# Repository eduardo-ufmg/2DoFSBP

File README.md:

# 2DoFSBP
A two degrees of freedom self balancing pendulum.
3D Drawing: https://cad.onshape.com/documents/dcaab3bd08b5da9e1fdd55d0/

# TODO

## Printing
- [ ] Print a half-wheel pair
- [ ] Conclude motor identification before proceeding
- [ ] Print and test a motor connector
- [ ] Print and test the base
- [ ] Print and test a connector for the wheel guard
- [ ] Print and test a wheel guard
- [ ] Print and test the second set

## Motor Identification
- [ ] Test motor
- [ ] Gather the following information
  - Is the PWM signal active low or active high?
  - Which level in the motor's DIR pin makes it rotate counterclockwise (from the motor's perspective, rather than facing its front)?
  - When the motor is rotating counterclockwise, does the encoder output from [this api](https://github.com/madhephaestus/ESP32Encoder) increment or decrement? (use attachFullQuad and consider 400 pulses per revolution)
- [ ] Create a class for the motor
  - Input signal must be a float in [-1, 1]
  - -1 → max speed clockwise, 1 → max speed counterclockwise
- [ ] Create a class for the encoder
  - Counterclockwise movement increments its position, clockwise decrements it
- [ ] Test both classes
- [ ] Write the code for the identification procedure
  - [ ] Microcontroller
    - Not supposed to compute speed online. Simply collect and transmit the encoder position readings.
    - Use a series of steps large enough for it to approach steady state, but not enough for it to reach it. (See PRBS identification)
    - Collect the input signal to the motor's object and the output signal from the encoder's object at 10 ms
    - Send data to the host at each sampling
    - Avoid blocking operations
  - [ ] Host
    - Listen for the experiment data
    - Store the experiment data when it is finished
    - Preprocess it
      - Remove invalid lines
      - Compute speed and acceleration from the position
    - Fit a standard DC motor transfer function
    - Store it and any available statistic about it
    - Extend it so U(s) is the input signal to the motor's object and Y(s) is the wheel torque
- [ ] Write the code for the model validation procedure
  - [ ] Microcontroller
    - Use the same code that was used for the identification
  - [ ] Host
    - Same acquisition and preprocessing as in the identification procedure
    - Simulate the model for the collected input
    - Compare its output to the captured output from the system

## Pendulum Modeling
- [ ] Capture a simplified geometric model
- [ ] Model the MIMO system with inputs T1 and T2 and outputs Theta and Phi, where:
  - T1 is the torque of the motor that controls Theta
  - T2 is the torque of the motor that controls Phi
  - Theta is the pitch angle
  - Phi is the roll angle
  - Coupling is to be considered

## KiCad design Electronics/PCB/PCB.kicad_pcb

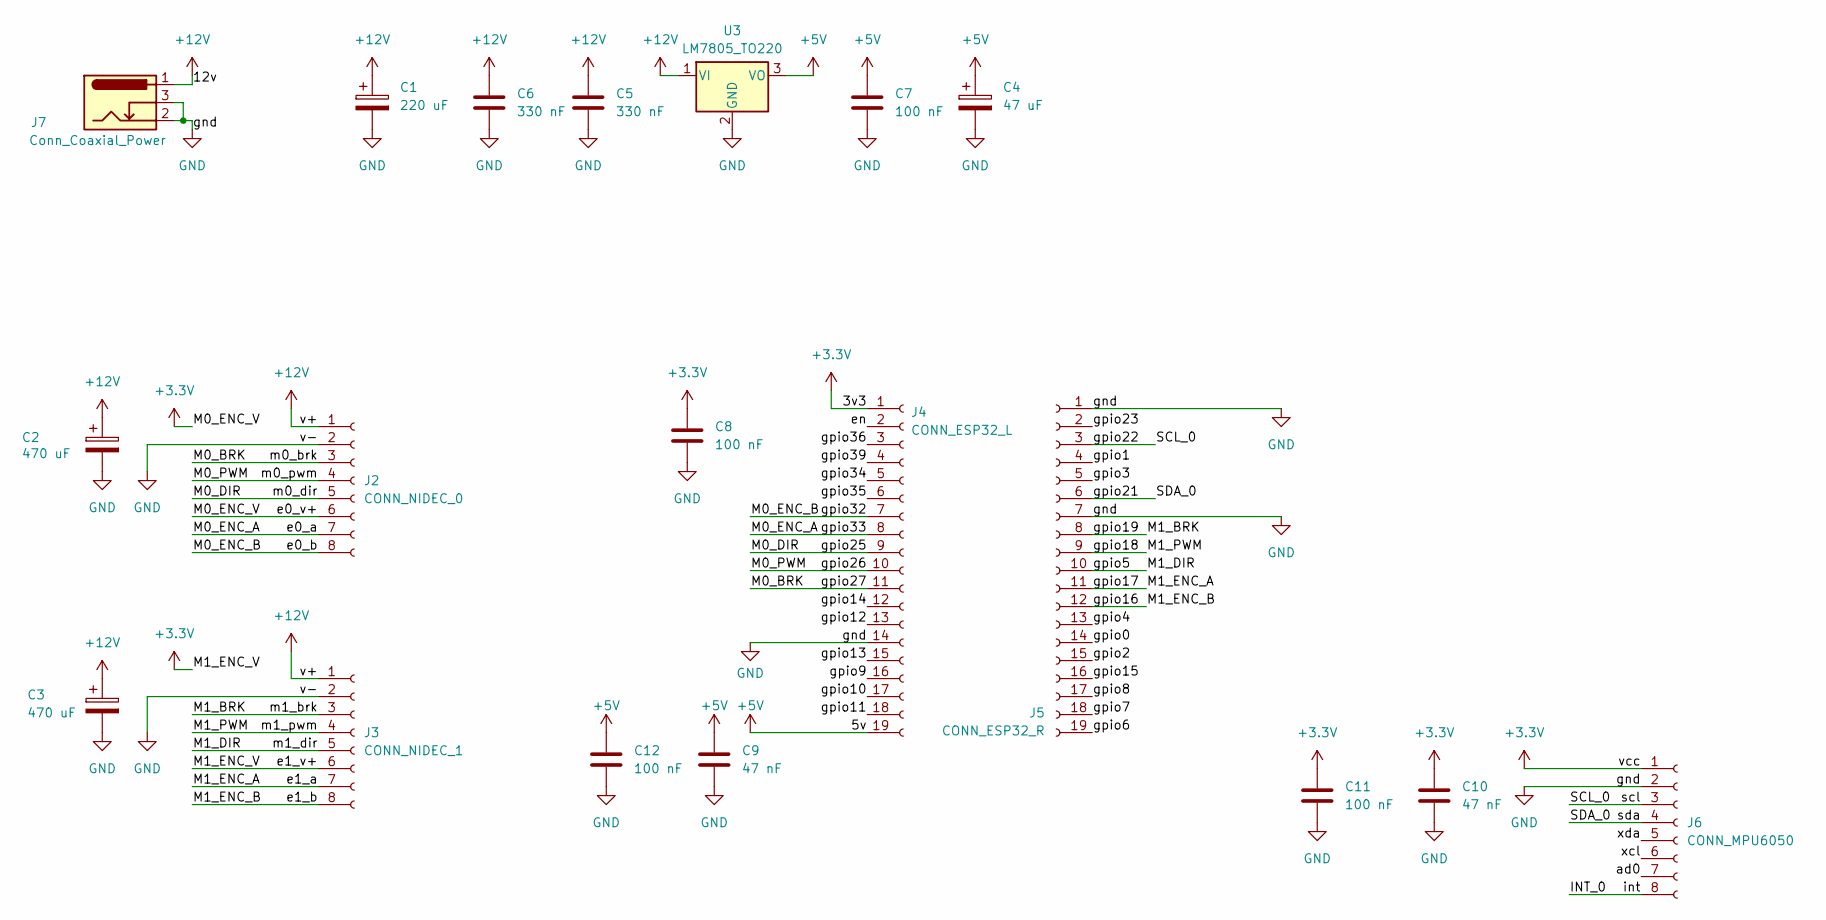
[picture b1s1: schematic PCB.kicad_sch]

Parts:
C1: 220 uF; CP_Radial_D8.0mm_P3.50mm
C2, C3: 470 uF; CP_Radial_D10.0mm_P5.00mm
C4: 47 uF; CP_Radial_D6.3mm_P2.50mm
C5, C6: 330 nF; C_Rect_L7.0mm_W2.5mm_P5.00mm
C7, C8, C11, C12: 100 nF; C_Disc_D3.0mm_W2.0mm_P2.50mm
C9, C10: 47 nF; C_Disc_D3.0mm_W2.0mm_P2.50mm
J2: CONN_NIDEC_0; JST_EH_B8B-EH-A_1x08_P2.50mm_Vertical
J3: CONN_NIDEC_1; JST_EH_B8B-EH-A_1x08_P2.50mm_Vertical
J4: CONN_ESP32_L; PinSocket_1x19_P2.54mm_Vertical
J5: CONN_ESP32_R; PinSocket_1x19_P2.54mm_Vertical
J6: CONN_MPU6050; PinSocket_1x08_P2.54mm_Vertical
J7: Conn_Coaxial_Power; BarrelJack_Horizontal
U3: LM7805_TO220; TO-220-3_Vertical

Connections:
+3.3V: C8.1, C10.1, C11.1, J2.6, J3.6, J4.1, J6.1
+5V: C4.1, C7.1, C9.1, C12.1, J4.19, U3.3 (VO)
+12V: C1.1, C2.1, C3.1, C5.1, C6.1, J2.1, J3.1, J7.1, U3.1 (VI)
/INT_0: J6.8
/M0_BRK: J2.3, J4.11
/M0_DIR: J2.5, J4.9
/M0_ENC_A: J2.7, J4.8
/M0_ENC_B: J2.8, J4.7
/M0_PWM: J2.4, J4.10
/M1_BRK: J3.3, J5.8
/M1_DIR: J3.5, J5.10
/M1_ENC_A: J3.7, J5.11
/M1_ENC_B: J3.8, J5.12
/M1_PWM: J3.4, J5.9
/SCL_0: J5.3, J6.3
/SDA_0: J5.6, J6.4
/ad0: J6.7
/en: J4.2
/gpio0: J5.14
/gpio1: J5.4
/gpio2: J5.15
/gpio3: J5.5
/gpio4: J5.13
/gpio6: J5.19
/gpio7: J5.18
/gpio8: J5.17
/gpio9: J4.16
/gpio10: J4.17
/gpio11: J4.18
/gpio12: J4.13
/gpio13: J4.15
/gpio14: J4.12
/gpio15: J5.16
/gpio23: J5.2
/gpio34: J4.5
/gpio35: J4.6
/gpio36: J4.3
/gpio39: J4.4
/xcl: J6.6
/xda: J6.5
GND: C1.2, C2.2, C3.2, C4.2, C5.2, C6.2, C7.2, C8.2, C9.2, C10.2, C11.2, C12.2, J2.2, J3.2, J4.14, J5.1, J5.7, J6.2, J7.2, J7.3, U3.2 (GND)

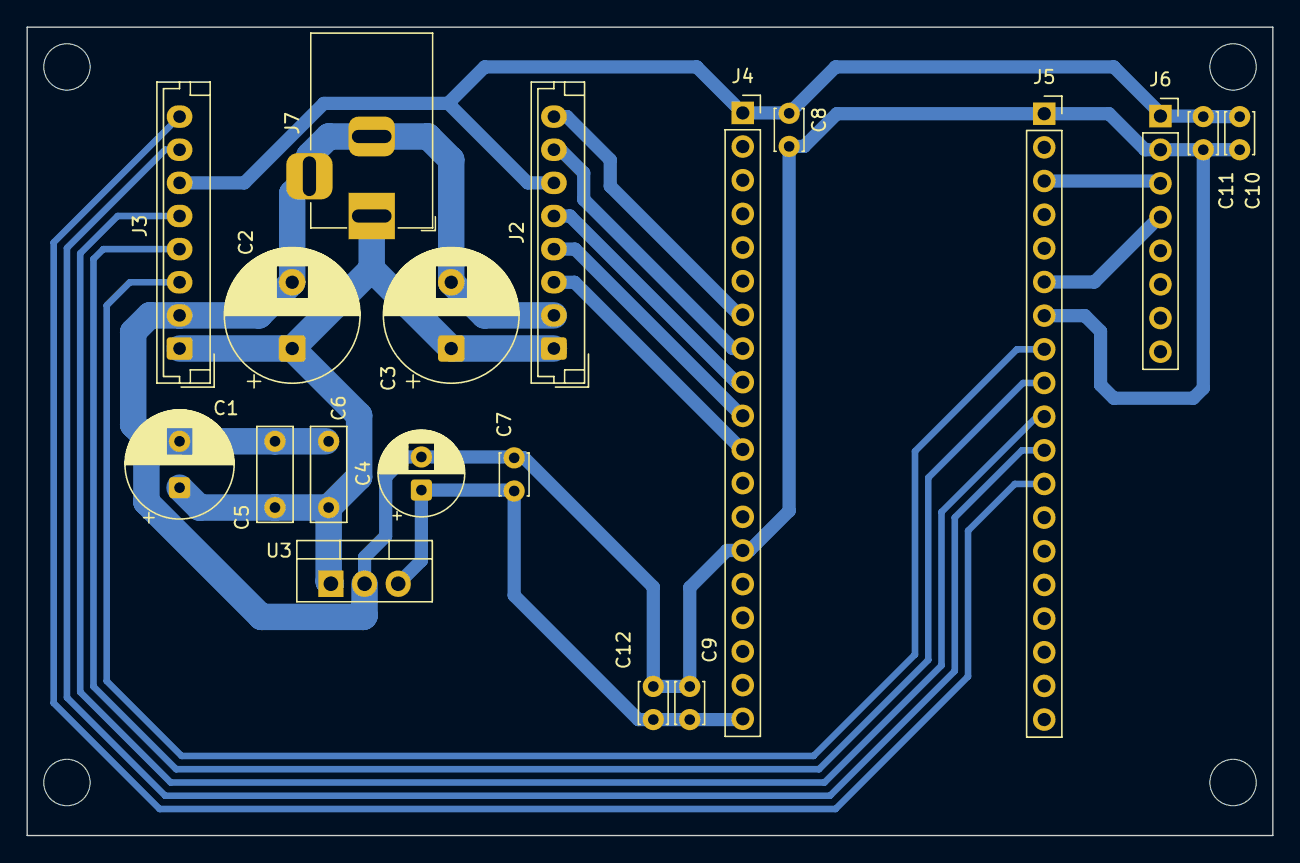
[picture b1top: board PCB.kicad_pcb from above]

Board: 2 copper layers, 94.0 x 61.0 mm, 19 parts (0 on the bottom side), 16 nets.

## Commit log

2025-08-26 name esp conn pins
2025-08-26 assign footprints
2025-08-27 export mainboard step
2025-08-28 improve PCB
2025-08-28 Add 3D drawing link to README
2025-08-30 drawn pcb
2025-09-02 fix pcb
2025-09-02 fix hole placement
2025-09-24 Revise TODO.md with additional tasks and clarifications
    Updated TODO list with detailed tasks for microcontroller and host responsibilities.
2025-09-24 Fix TODO formatting
2025-09-24 Update visible layers in PCB files and set BOM export filename path
2025-09-24 Consolidate TODO items into README.md and remove TODO.md
2025-09-27 Update TODO list in README.md
    Removed mechanical project tasks from the TODO list.
2025-10-29 Add initial implementations for experiment, estimation, and validation modules
    - Created estimate.py to handle data reading, cleaning, and computation of velocity and acceleration, along with torque estimation.
    - Developed experiment.py for managing the experiment lifecycle, including connection checks, data acquisition, and success reporting.
    - Implemented validate.py to facilitate validation processes, including input signal capture, model comparison, and result reporting.
2025-11-13 Add initial identification project structure with configuration and source files
2025-11-13 Change controller project name
2025-11-13 Implement communication functions for motor control and data handling
2025-11-13 Implement the experiment script
2025-11-13 Improve logging and plot data
2025-11-13 Save time instead of index
2025-11-13 Implement estimation
2025-11-13 Estimate and validade
2025-11-13 Rename validation results image and update save message
2025-11-15 Refactor test to: - ensure a more consistent 100 Hz sampling rate by changing the fixed delay for a timing monitor that checks the remaining time until the next sample - fill a vector with random val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
2025-11-15 Refactor estimation to estimate a dynamic input/position
2025-11-15 Refactor experiment and validation scripts to improve connection handling and update data processing for dynamic velocity model
2025-11-17 Latest STLs
2025-11-18 Remove obsolete validation results image from the host directory
2025-11-18 simple arx
2025-11-18 improve arc
2025-11-18 save comparisson figure
2025-11-18 Update experiment data summary and results
    - Modified model parameters in experiment_data_id_summary.json:
    - Increased na from 4 to 5 and nb from 1 to 3.
    - Adjusted alpha from 0.0 to 0.01.
    - Updated theta values for improved model accuracy.
    - Revised matrix A to include additional rows and columns.
    - Changed matrix B to reflect new model structure.
2025-11-18 Use identified model to estimate the internal states
2025-11-18 Reset identification
2025-11-19 Excelent identification results
2025-11-19 First design iteration, to be improved
2025-11-19 Add random steps waveform functionality and update simulation metrics
2025-11-19 Restart design: instead of controlling troque, the esp is to compute the dynamic position from torque and controll the position
2025-11-20 Start motor control tests
2025-11-22 Go back to rise time constant input time
2025-11-22 Remove unused step response plot image from the host directory
2025-11-22 Remove obsolete files and directories related to motor control and identification
2025-11-22 Refactor CSV header format and remove obsolete identification files
2025-11-22 feat: Implement motor identification and dynamics analysis
    - Added `identification.py` for motor dynamics identification using regression analysis.
    - Introduced preprocessing steps with Savitzky-Golay filter for smoothing and differentiation.
    - Calculated net torque and fitted a linear model to estimate motor parameters (K, b, c).
    - Results are saved in both JSON and NPZ formats for further analysis.
    - Included visualization of input, computed speed, and torque dynamics.
    - Added `.clang-format` for consistent code formatting.
2025-11-22 Test feedback controller
2025-11-22 Add MotorFeedforward class for model-based motor control
    - Implemented MotorFeedforward class in MotorFeedForward.cpp and MotorFeedForward.h.
    - The class provides functionality to compute the required control input to achieve a desired torque while compensating for friction and back-EMF.
    - Added methods for setting output limits and updating model parameters.
    - Included input validation to prevent division by zero and ensure valid output limits.
2025-11-22 Allow faster controller change
2025-11-22 Remove motor_control
2025-11-22 prepare multiple controllers
